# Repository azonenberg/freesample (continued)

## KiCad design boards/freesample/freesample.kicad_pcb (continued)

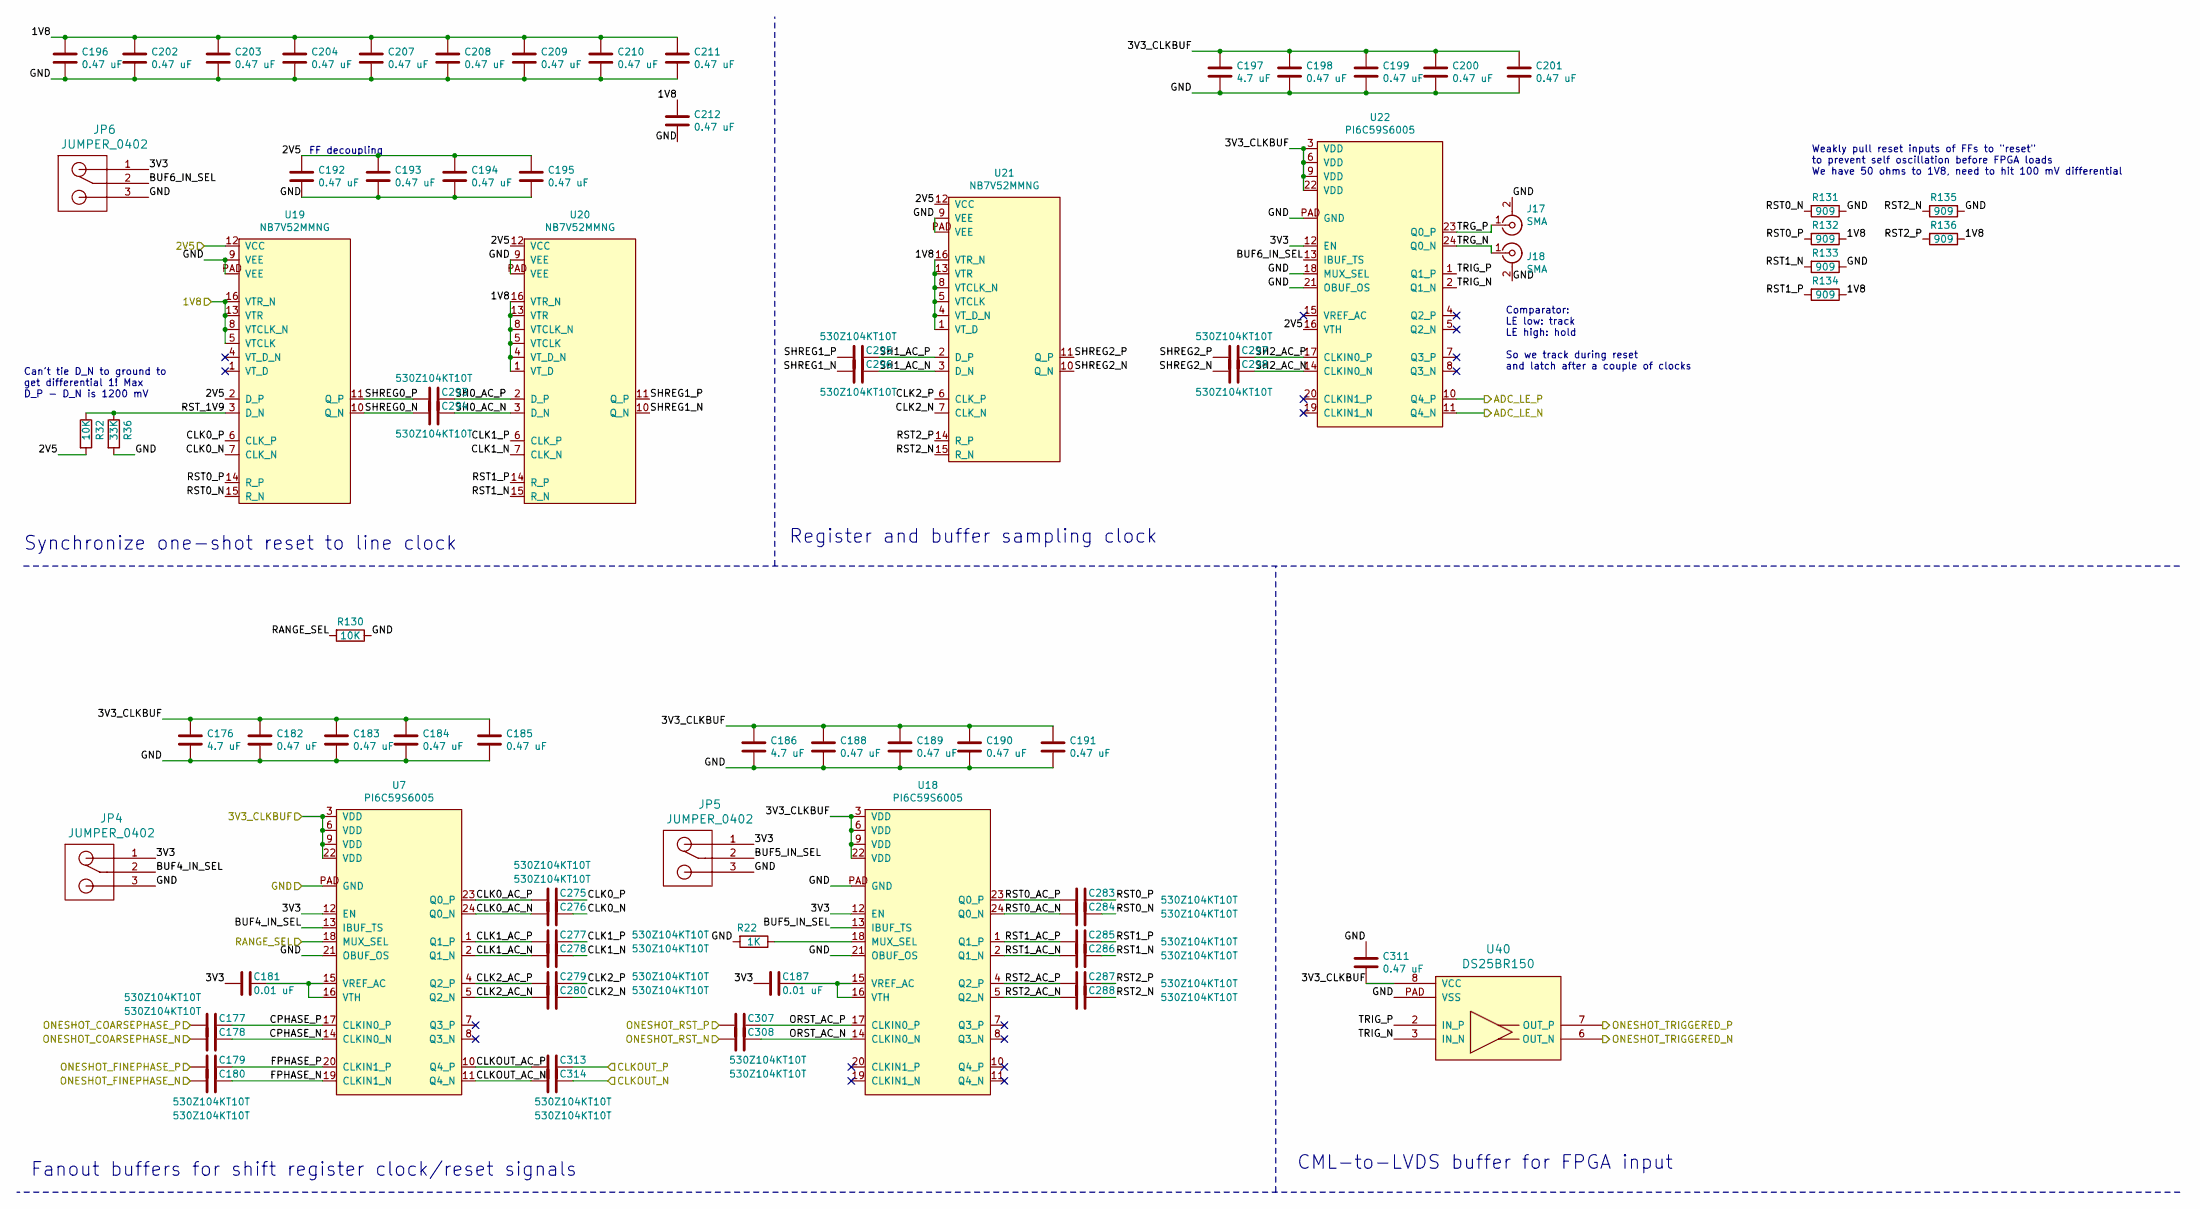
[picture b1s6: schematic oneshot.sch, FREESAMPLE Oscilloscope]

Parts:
C176, C186, C197: 4.7 uF; EIA_0603_CAP_NOSILK
C177, C178, C179, C180, C275, C276, C277, C278, C279, C280, C283, C284, C285, C286, C287, C288, C293, C294, C295, C296, C297, C298, C307, C308, C313, C314: 530Z104KT10T; EIA_0201_CAP_NOSILK
C181, C187: 0.01 uF; EIA_0402_CAP_NOSILK
C182, C183, C184, C185, C188, C189, C190, C191, C192, C193, C194, C195, C196, C198, C199, C200, C201, C202, C203, C204, C207, C208, C209, C210, C211, C212, C311: 0.47 uF; EIA_0402_CAP_NOSILK
J17, J18: SMA; CONN_SMA_EDGE_SAMTEC_SMA_J_P_H_ST_EM1
JP4, JP5, JP6: JUMPER_0402; EIA_0402_JUMPER
R22: 1K; EIA_0402_RES_NOSILK
R32, R130: 10K; EIA_0402_RES_NOSILK
R36: 33K; EIA_0402_RES_NOSILK
R131, R132, R133, R134, R135, R136: 909; EIA_0402_RES_NOSILK
U7, U18, U22: PI6C59S6005; QFN_24_0.5MM_4x4MM
U19, U20, U21: NB7V52MMNG; QFN_16_0.5MM_3x3MM
U40: DS25BR150; DFN_8_0.5MM_3x3MM

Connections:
/1V8: C196.1, C202.1, C203.1, C204.1, C207.1, C208.1, C209.1, C210.1, C211.1, C212.1, R132.1, R134.1, R136.1, U19.5 (VTCLK), U19.8 (VTCLK_N), U19.13 (VTR), U19.16 (VTR_N), U20.1 (VT_D), U20.4 (VT_D_N), U20.5 (VTCLK), U20.8 (VTCLK_N), U20.13 (VTR), U20.16 (VTR_N), U21.1 (VT_D), U21.4 (VT_D_N), U21.5 (VTCLK), U21.8 (VTCLK_N), U21.13 (VTR), U21.16 (VTR_N); also elsewhere on the board
/2V5: C192.1, C193.1, C194.1, C195.1, R32.2, U19.2 (D_P), U19.12 (VCC), U20.12 (VCC), U21.12 (VCC), U22.16 (VTH); also elsewhere on the board
/3V3_CLKBUF: C176.1, C182.1, C183.1, C184.1, C185.1, C186.1, C188.1, C189.1, C190.1, C191.1, C197.1, C198.1, C199.1, C200.1, C201.1, C311.2, U7.3 (VDD), U7.6 (VDD), U7.9 (VDD), U7.22 (VDD), U18.3 (VDD), U18.6 (VDD), U18.9 (VDD), U18.22 (VDD), U22.3 (VDD), U22.6 (VDD), U22.9 (VDD), U22.22 (VDD), U40.8 (VCC); also elsewhere on the board
/ADC/ADC_LE_N: U22.11 (Q4_N); also elsewhere on the board
/ADC/ADC_LE_P: U22.10 (Q4_P); also elsewhere on the board
/GND: C176.2, C182.2, C183.2, C184.2, C185.2, C186.2, C188.2, C189.2, C190.2, C191.2, C192.2, C193.2, C194.2, C195.2, C196.2, C197.2, C198.2, C199.2, C200.2, C201.2, C202.2, C203.2, C204.2, C207.2, C208.2, C209.2, C210.2, C211.2, C212.2, C311.1, J17.2 (Ext), J18.2 (Ext), JP4.3, JP5.3, JP6.3, R22.2, R36.2, R130.1, R131.1, R133.1, R135.1, U7.21 (OBUF_OS), U7.PAD (GND), U18.21 (OBUF_OS), U18.PAD (GND), U19.9 (VEE), U19.PAD (VEE), U20.9 (VEE), U20.PAD (VEE), U21.9 (VEE), U21.PAD (VEE), U22.18 (MUX_SEL), U22.21 (OBUF_OS), U22.PAD (GND), U40.PAD (VSS); also elsewhere on the board
/ONESHOT_RST_N: C308.2; also elsewhere on the board
/ONESHOT_RST_P: C307.2; also elsewhere on the board
/One-Shot/3V3: C181.2, C187.2, JP4.1, JP5.1, JP6.1, U7.12 (EN), U18.12 (EN), U22.12 (EN)
/One-Shot/BUF4_IN_SEL: JP4.2, U7.13 (IBUF_TS)
/One-Shot/BUF5_IN_SEL: JP5.2, U18.13 (IBUF_TS)
/One-Shot/BUF6_IN_SEL: JP6.2, U22.13 (IBUF_TS)
/One-Shot/CLK0_AC_N: C276.2, U7.24 (Q0_N)
/One-Shot/CLK0_AC_P: C275.2, U7.23 (Q0_P)
/One-Shot/CLK0_N: C276.1, U19.7 (CLK_N)
/One-Shot/CLK0_P: C275.1, U19.6 (CLK_P)
/One-Shot/CLK1_AC_N: C278.2, U7.2 (Q1_N)
/One-Shot/CLK1_AC_P: C277.2, U7.1 (Q1_P)
/One-Shot/CLK1_N: C278.1, U20.7 (CLK_N)
/One-Shot/CLK1_P: C277.1, U20.6 (CLK_P)
/One-Shot/CLK2_AC_N: C280.2, U7.5 (Q2_N)
/One-Shot/CLK2_AC_P: C279.2, U7.4 (Q2_P)
/One-Shot/CLK2_N: C280.1, U21.7 (CLK_N)
/One-Shot/CLK2_P: C279.1, U21.6 (CLK_P)
/One-Shot/CLKOUT_AC_N: C314.2, U7.11 (Q4_N)
/One-Shot/CLKOUT_AC_P: C313.2, U7.10 (Q4_P)
/One-Shot/CLKOUT_N: C314.1; also elsewhere on the board
/One-Shot/CLKOUT_P: C313.1; also elsewhere on the board
/One-Shot/CPHASE_N: C178.1, U7.14 (CLKIN0_N)
/One-Shot/CPHASE_P: C177.1, U7.17 (CLKIN0_P)
/One-Shot/FPHASE_N: C180.1, U7.19 (CLKIN1_N)
/One-Shot/FPHASE_P: C179.1, U7.20 (CLKIN1_P)
/One-Shot/ORST_AC_N: C308.1, U18.14 (CLKIN0_N)
/One-Shot/ORST_AC_P: C307.1, U18.17 (CLKIN0_P)
/One-Shot/RST0_AC_N: C284.2, U18.24 (Q0_N)
/One-Shot/RST0_AC_P: C283.2, U18.23 (Q0_P)
/One-Shot/RST0_N: C284.1, R131.2, U19.15 (R_N)
/One-Shot/RST0_P: C283.1, R132.2, U19.14 (R_P)
/One-Shot/RST1_AC_N: C286.2, U18.2 (Q1_N)
/One-Shot/RST1_AC_P: C285.2, U18.1 (Q1_P)
/One-Shot/RST1_N: C286.1, R133.2, U20.15 (R_N)
/One-Shot/RST1_P: C285.1, R134.2, U20.14 (R_P)
/One-Shot/RST2_AC_N: C288.2, U18.5 (Q2_N)
/One-Shot/RST2_AC_P: C287.2, U18.4 (Q2_P)
/One-Shot/RST2_N: C288.1, R135.2, U21.15 (R_N)
/One-Shot/RST2_P: C287.1, R136.2, U21.14 (R_P)
/One-Shot/RST_1V9: R32.1, R36.1, U19.3 (D_N)
/One-Shot/SH0_AC_N: C294.1, U20.3 (D_N)
/One-Shot/SH0_AC_P: C293.1, U20.2 (D_P)
/One-Shot/SH1_AC_N: C296.1, U21.3 (D_N)
/One-Shot/SH1_AC_P: C295.1, U21.2 (D_P)
/One-Shot/SH2_AC_N: C298.1, U22.14 (CLKIN0_N)
/One-Shot/SH2_AC_P: C297.1, U22.17 (CLKIN0_P)
/One-Shot/SHREG0_N: C294.2, U19.10 (Q_N)
/One-Shot/SHREG0_P: C293.2, U19.11 (Q_P)
/One-Shot/SHREG1_N: C296.2, U20.10 (Q_N)
/One-Shot/SHREG1_P: C295.2, U20.11 (Q_P)
/One-Shot/SHREG2_N: C298.2, U21.10 (Q_N)
/One-Shot/SHREG2_P: C297.2, U21.11 (Q_P)
/One-Shot/TRG_N: J18.1 (In), U22.24 (Q0_N)
/One-Shot/TRG_P: J17.1 (In), U22.23 (Q0_P)
/One-Shot/TRIG_N: U22.2 (Q1_N), U40.3 (IN_N)
/One-Shot/TRIG_P: U22.1 (Q1_P), U40.2 (IN_P)
/Phase control/COARSEPHASE_N: C178.2; also elsewhere on the board
/Phase control/COARSEPHASE_P: C177.2; also elsewhere on the board
/Phase control/FINEPHASE_N: C180.2; also elsewhere on the board
/Phase control/FINEPHASE_P: C179.2; also elsewhere on the board
/RANGE_SEL: R130.2, U7.18 (MUX_SEL); also elsewhere on the board
/TRIGGERED_N: U40.6 (OUT_N); also elsewhere on the board
/TRIGGERED_P: U40.7 (OUT_P); also elsewhere on the board
unnamed: C181.1, U7.15 (VREF_AC), U7.16 (VTH)
unnamed: C187.1, U18.15 (VREF_AC), U18.16 (VTH)
unnamed: R22.1, U18.18 (MUX_SEL)

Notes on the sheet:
FF decoupling
Synchronize one-shot reset to line clock
Register and buffer sampling clock
Can't tie D_N to ground to get differential 1! Max D_P - D_N is 1200 mV
CML-to-LVDS buffer for FPGA input
Comparator: LE low: track LE high: hold So we track during reset and latch after a couple of clocks
Fanout buffers for shift register clock/reset signals
Weakly pull reset inputs of FFs to "reset" to prevent self oscillation before FPGA loads We have 50 ohms to 1V8, need to hit 100 mV differential

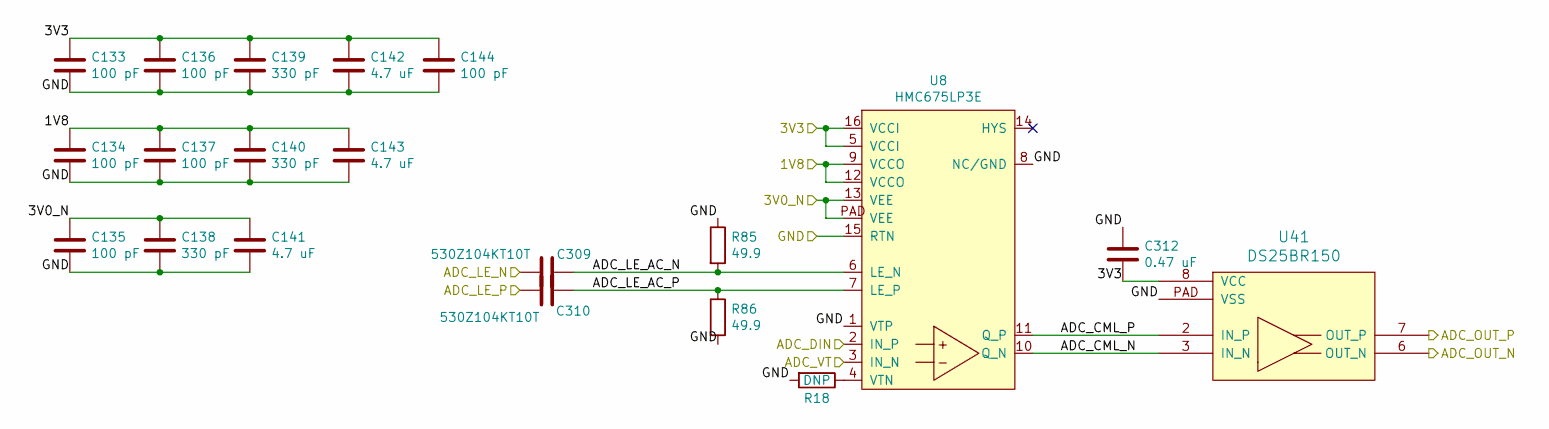
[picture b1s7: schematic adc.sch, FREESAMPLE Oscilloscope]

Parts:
C133, C134, C135, C136, C137, C144: 100 pF; EIA_0201_CAP_NOSILK
C138, C139, C140: 330 pF; EIA_0201_CAP_NOSILK
C141, C142, C143: 4.7 uF; EIA_0603_CAP_NOSILK
C309, C310: 530Z104KT10T; EIA_0201_CAP_NOSILK
C312: 0.47 uF; EIA_0402_CAP_NOSILK
R18: DNP; EIA_0402_RES_NOSILK
R85, R86: 49.9; EIA_0402_RES_NOSILK
U8: HMC675LP3E; QFN_16_0.5MM_3x3MM
U41: DS25BR150; DFN_8_0.5MM_3x3MM

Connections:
/1V8: C134.1, C137.1, C140.1, C143.1, U8.9 (VCCO), U8.12 (VCCO); also elsewhere on the board
/3V0_N: C135.1, C138.1, C141.1, U8.13 (VEE), U8.PAD (VEE); also elsewhere on the board
/3V3: C133.1, C136.1, C139.1, C142.1, C144.1, C312.2, U8.5 (VCCI), U8.16 (VCCI), U41.8 (VCC); also elsewhere on the board
/ADC/ADC_CML_N: U8.10 (Q_N), U41.3 (IN_N)
/ADC/ADC_CML_P: U8.11 (Q_P), U41.2 (IN_P)
/ADC/ADC_LE_AC_N: C309.1, R85.2, U8.6 (LE_N)
/ADC/ADC_LE_AC_P: C310.1, R86.1, U8.7 (LE_P)
/ADC/ADC_LE_N: C309.2; also elsewhere on the board
/ADC/ADC_LE_P: C310.2; also elsewhere on the board
/ADC_DIN: U8.2 (IN_P); also elsewhere on the board
/ADC_OUT_N: U41.6 (OUT_N); also elsewhere on the board
/ADC_OUT_P: U41.7 (OUT_P); also elsewhere on the board
/ADC_VT: U8.3 (IN_N); also elsewhere on the board
/GND: C133.2, C134.2, C135.2, C136.2, C137.2, C138.2, C139.2, C140.2, C141.2, C142.2, C143.2, C144.2, C312.1, R18.2, R85.1, R86.2, U8.1 (VTP), U8.8 (NC/GND), U8.15 (RTN), U41.PAD (VSS); also elsewhere on the board
unnamed: R18.1, U8.4 (VTN)

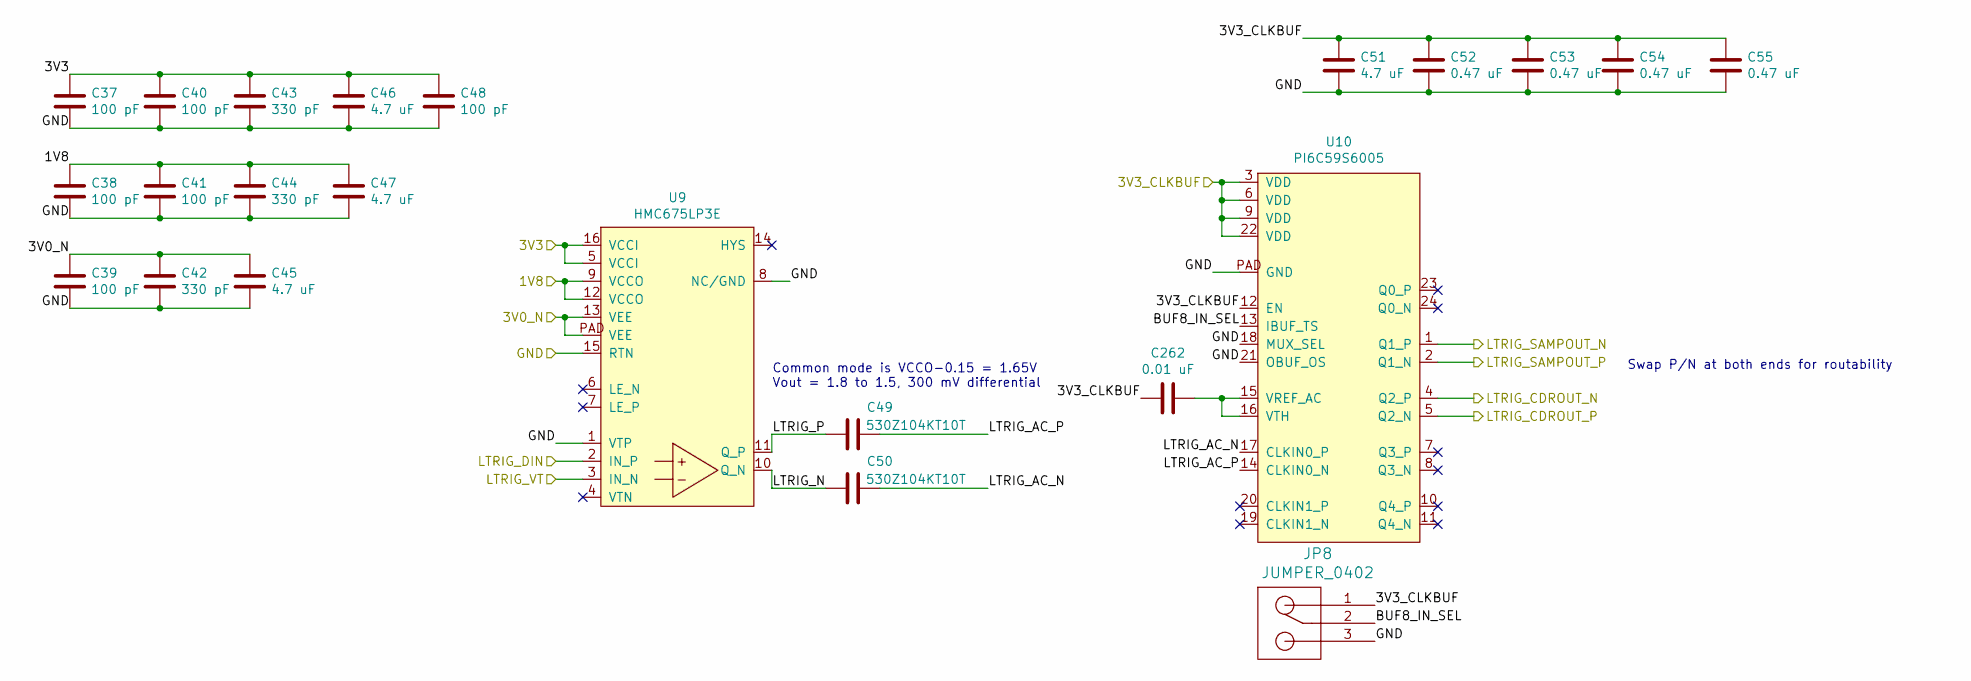
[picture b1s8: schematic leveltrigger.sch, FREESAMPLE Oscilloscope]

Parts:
C37, C38, C39, C40, C41, C48: 100 pF; EIA_0201_CAP_NOSILK
C42, C43, C44: 330 pF; EIA_0201_CAP_NOSILK
C45, C46, C47, C51: 4.7 uF; EIA_0603_CAP_NOSILK
C49, C50: 530Z104KT10T; EIA_0201_CAP_NOSILK
C52, C53, C54, C55: 0.47 uF; EIA_0402_CAP_NOSILK
C262: 0.01 uF; EIA_0402_CAP_NOSILK
JP8: JUMPER_0402; EIA_0402_JUMPER
U9: HMC675LP3E; QFN_16_0.5MM_3x3MM
U10: PI6C59S6005; QFN_24_0.5MM_4x4MM

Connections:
/1V8: C38.1, C41.1, C44.1, C47.1, U9.9 (VCCO), U9.12 (VCCO); also elsewhere on the board
/3V0_N: C39.1, C42.1, C45.1, U9.13 (VEE), U9.PAD (VEE); also elsewhere on the board
/3V3: C37.1, C40.1, C43.1, C46.1, C48.1, U9.5 (VCCI), U9.16 (VCCI); also elsewhere on the board
/3V3_CLKBUF: C51.1, C52.1, C53.1, C54.1, C55.1, C262.2, JP8.1, U10.3 (VDD), U10.6 (VDD), U10.9 (VDD), U10.12 (EN), U10.22 (VDD); also elsewhere on the board
/CDR/CDR_DIN_N: U10.4 (Q2_P); also elsewhere on the board
/CDR/CDR_DIN_P: U10.5 (Q2_N); also elsewhere on the board
/GND: C37.2, C38.2, C39.2, C40.2, C41.2, C42.2, C43.2, C44.2, C45.2, C46.2, C47.2, C48.2, C51.2, C52.2, C53.2, C54.2, C55.2, JP8.3, U9.1 (VTP), U9.8 (NC/GND), U9.15 (RTN), U10.18 (MUX_SEL), U10.21 (OBUF_OS), U10.PAD (GND); also elsewhere on the board
/LTRIG_DIN: U9.2 (IN_P); also elsewhere on the board
/LTRIG_VT: U9.3 (IN_N); also elsewhere on the board
/Level triggering/BUF8_IN_SEL: JP8.2, U10.13 (IBUF_TS)
/Level triggering/LTRIG_AC_N: C50.1, U10.17 (CLKIN0_P)
/Level triggering/LTRIG_AC_P: C49.1, U10.14 (CLKIN0_N)
/Level triggering/LTRIG_N: C50.2, U9.10 (Q_N)
/Level triggering/LTRIG_P: C49.2, U9.11 (Q_P)
/Level triggering/LTRIG_SAMPOUT_N: U10.1 (Q1_P); also elsewhere on the board
/Level triggering/LTRIG_SAMPOUT_P: U10.2 (Q1_N); also elsewhere on the board
unnamed: C262.1, U10.15 (VREF_AC), U10.16 (VTH)

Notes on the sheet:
Common mode is VCCO-0.15 = 1.65V Vout = 1.8 to 1.5, 300 mV differential
Swap P/N at both ends for routability

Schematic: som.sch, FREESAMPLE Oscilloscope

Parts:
C129, C130, C131, C132, C321: 0.1 uF; EIA_0402_CAP_NOSILK
J7: CONN_INTEGRALSTICK_FPGA_HOST; CONN_SAMTEC_QSH-060-01-L-D-A
J8: CONN_INTEGRALSTICK_MCU_HOST; CONN_SAMTEC_QSH-060-01-L-D-A
J9: 0826-1G1T-23-F; CONN_BELFUSE_0826_1G1T_23_F
J10: XILINX_JTAG; XILINX_JTAG_PTH_MOLEX_0878311420
J19, J20, J21: JUMPER; CONN_HEADER_2.54MM_1x2
J24, J25: SMA; CONN_SMA_EDGE_SAMTEC_SMA_J_P_H_ST_EM1
J26: PMOD_HOST; CONN_HEADER_2.54MM_2x6_RA_PMOD_HOST
Q1: SSM6N58NU; DFN_6_0.65MM_2x2MM_GDS
R16, R17: 470; EIA_0402_RES_NOSILK
TP32, TP33, TP34, TP35: GROUNDCLIP; TESTPOINT_SMT_KEYSTONE_5016

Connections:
/5V25: J7.1 (5V0), J7.2 (5V0), J7.3 (5V0), J7.4 (5V0), J7.5 (5V0), J7.6 (5V0); also elsewhere on the board
/ADC_OUT_N: J7.16 (LVDS_DQ6_N); also elsewhere on the board
/ADC_OUT_P: J7.18 (LVDS_DQ6_P); also elsewhere on the board
/COARSE_EN: J7.97 (IO_3V3); also elsewhere on the board
/COARSE_SCLK: J7.102 (IO_3V3); also elsewhere on the board
/COARSE_SDIN: J7.101 (IO_3V3); also elsewhere on the board
/COARSE_SLOAD: J7.98 (IO_3V3); also elsewhere on the board
/D3V3: J7.69 (3V3), J7.70 (3V3), J7.75 (3V3), J7.76 (3V3), J7.81 (3V3), J7.82 (3V3), J7.87 (3V3), J7.88 (3V3), J7.93 (3V3), J7.94 (3V3), J7.99 (3V3), J7.100 (3V3), J7.105 (3V3), J7.106 (3V3), J7.111 (3V3), J7.112 (3V3), J7.117 (3V3), J7.118 (3V3), J8.1 (3V3), J8.7 (3V3), J8.13 (3V3), J8.19 (3V3), J8.25 (3V3), J8.31 (3V3), J8.32 (3V3), J8.37 (3V3), J8.38 (3V3), J8.43 (3V3), J8.44 (3V3), J8.49 (3V3), J8.50 (3V3), J8.55 (3V3), J8.56 (3V3), J8.61 (3V3), J8.62 (3V3), J8.67 (3V3), J8.68 (3V3), J8.73 (3V3), J8.74 (3V3), J8.79 (3V3), J8.80 (3V3), J8.85 (3V3), J8.86 (3V3), J8.91 (3V3), J8.92 (3V3), J8.97 (3V3), J8.98 (3V3), J8.103 (3V3), J8.104 (3V3), J8.109 (3V3), J8.110 (3V3), J8.115 (3V3), J8.116 (3V3), J10.2 (Vccaux), J21.2, J26.6 (3V3), J26.12 (3V3), R16.2, R17.2; also elsewhere on the board
/DAC_CS_N: J7.67 (IO_1V8); also elsewhere on the board
/DAC_MISO: J7.62 (IO_1V8); also elsewhere on the board
/DAC_MOSI: J7.65 (IO_1V8); also elsewhere on the board
/DAC_MUXOUT: J8.111 (PF3); also elsewhere on the board
/DAC_RST_N: J7.61 (IO_1V8); also elsewhere on the board
/DAC_SCK: J7.66 (IO_1V8); also elsewhere on the board
/EXT_CLK_SEL: J7.73 (IO_3V3); also elsewhere on the board
/FINE_SEL0_N: J7.34 (LVDS_DQ0_N); also elsewhere on the board
/FINE_SEL0_P: J7.36 (LVDS_DQ0_P); also elsewhere on the board
/FINE_SEL1_N: J7.33 (LVDS_DQ1_N); also elsewhere on the board
/FINE_SEL1_P: J7.35 (LVDS_DQ1_P); also elsewhere on the board
/FINE_SEL2_N: J7.28 (LVDS_DQ2_N); also elsewhere on the board
/FINE_SEL2_P: J7.30 (LVDS_DQ2_P); also elsewhere on the board
/FINE_SEL3_N: J7.27 (LVDS_DQ3_N); also elsewhere on the board
/FINE_SEL3_P: J7.29 (LVDS_DQ3_P); also elsewhere on the board
/FINE_SEL4_N: J7.22 (LVDS_DQ4_N); also elsewhere on the board
/FINE_SEL4_P: J7.24 (LVDS_DQ4_P); also elsewhere on the board
/FPGACLK_N: J7.107 (IO_3V3_CKN); also elsewhere on the board
/FPGACLK_P: J7.109 (IO_3V3_CKP); also elsewhere on the board
/GND: C129.1, C130.1, C131.1, C132.1, C321.2, J7.121 (GND), J7.122 (GND), J7.123 (GND), J7.124 (GND), J7.125 (GND), J7.126 (GND), J7.127 (GND), J7.128 (GND), J8.2 (GND), J8.8 (GND), J8.14 (GND), J8.20 (GND), J8.26 (GND), J8.121 (GND), J8.122 (GND), J8.123 (GND), J8.124 (GND), J8.125 (GND), J8.126 (GND), J8.127 (GND), J8.128 (GND), J10.3 (Vss), J10.5 (Vss), J10.7 (Vss), J10.9 (Vss), J10.11 (Vss), J19.2, J20.2, J24.2 (Ext), J25.2 (Ext), J26.5 (GND), J26.11 (GND), Q1.S1 (S), Q1.S2 (S), TP32.1, TP33.1, TP34.1, TP35.1; also elsewhere on the board
/LDAC_N: J7.68 (IO_1V8); also elsewhere on the board
/ONESHOT_RST_N: J7.21 (LVDS_DQ5_N); also elsewhere on the board
/ONESHOT_RST_P: J7.23 (LVDS_DQ5_P); also elsewhere on the board
/OSC_FS0: J7.79 (IO_3V3); also elsewhere on the board
/OSC_FS1: J7.78 (IO_3V3); also elsewhere on the board
/OSC_OE: J7.74 (IO_3V3); also elsewhere on the board
/OSC_OS: J7.77 (IO_3V3); also elsewhere on the board
/OSC_PWR_EN: J7.103 (IO_3V3); also elsewhere on the board
/PLL_CLK: J7.86 (IO_3V3); also elsewhere on the board
/PLL_CLKIN0: J7.90 (IO_3V3); also elsewhere on the board
/PLL_CLKIN1: J7.91 (IO_3V3); also elsewhere on the board
/PLL_DATA: J7.89 (IO_3V3); also elsewhere on the board
/PLL_HOLDOVER: J7.83 (IO_3V3); also elsewhere on the board
/PLL_LD: J7.84 (IO_3V3); also elsewhere on the board
/PLL_LE: J7.85 (IO_3V3); also elsewhere on the board
/PLL_SYNC: J7.80 (IO_3V3); also elsewhere on the board
/RANGE_SEL: J7.96 (IO_3V3); also elsewhere on the board
/SAMP_MUXSEL0: J7.92 (IO_3V3); also elsewhere on the board
/SAMP_MUXSEL1: J7.95 (IO_3V3); also elsewhere on the board
/SERDES_MDC: J7.56 (IO_1V8); also elsewhere on the board
/SERDES_MDIO: J7.55 (IO_1V8); also elsewhere on the board
/SERDES_MODE_SEL: J7.60 (IO_1V8); also elsewhere on the board
/SERDES_POWER_EN: J7.54 (IO_1V8); also elsewhere on the board
/SERDES_RST_N: J7.59 (IO_1V8); also elsewhere on the board
/SoM connectors/D1V8: J7.39 (1V8), J7.40 (1V8), J7.45 (1V8), J7.46 (1V8), J7.51 (1V8), J7.52 (1V8), J7.57 (1V8), J7.58 (1V8), J7.63 (1V8), J7.64 (1V8)
/SoM connectors/D2V5: J7.7 (2V5), J7.8 (2V5), J7.13 (2V5), J7.14 (2V5), J7.19 (2V5), J7.20 (2V5), J7.25 (2V5), J7.26 (2V5), J7.31 (2V5), J7.32 (2V5), J7.37 (2V5), J7.38 (2V5)
/SoM connectors/ETH_A_N: J8.6 (ETH_A_N), J9.10 (CH1_N)
/SoM connectors/ETH_A_P: J8.4 (ETH_A_P), J9.11 (CH1_P)
/SoM connectors/ETH_A_TAP: C129.2, J9.12 (CH1_TAP)
/SoM connectors/ETH_B_N: J8.12 (ETH_B_N), J9.5 (CH2_N)
/SoM connectors/ETH_B_P: J8.10 (ETH_B_P), J9.4 (CH2_P)
/SoM connectors/ETH_B_TAP: C130.2, J9.6 (CH2_TAP)
/SoM connectors/ETH_C_N: J8.18 (ETH_C_N), J9.2 (CH3_N)
/SoM connectors/ETH_C_P: J8.16 (ETH_C_P), J9.3 (CH3_P)
/SoM connectors/ETH_C_TAP: C131.2, J9.1 (CH3_TAP)
/SoM connectors/ETH_D_N: J8.24 (ETH_D_N), J9.9 (CH4_N)
/SoM connectors/ETH_D_P: J8.22 (ETH_D_P), J9.8 (CH4_P)
/SoM connectors/ETH_D_TAP: C132.2, J9.7 (CH4_TAP)
/SoM connectors/ETH_GND: C321.1, J9.17 (SHLD)
/SoM connectors/ETH_LED1_EN: J7.50 (IO_1V8), Q1.G2 (G)
/SoM connectors/ETH_LED1_N: J9.13 (LED1_N), Q1.D2 (D)
/SoM connectors/ETH_LED2_EN: J7.53 (IO_1V8), Q1.G1 (G)
/SoM connectors/ETH_LED2_N: J9.15 (LED2_N), Q1.D1 (D)
/SoM connectors/FPGA_RST_N: J8.76 (FPGA_RST_N), J19.1
/SoM connectors/GPIO0: J7.110 (IO_3V3), J26.1 (D0)
/SoM connectors/GPIO1: J7.113 (IO_3V3), J26.2 (D1)
/SoM connectors/GPIO2: J7.114 (IO_3V3), J26.3 (D2)
/SoM connectors/GPIO3: J7.115 (IO_3V3), J26.4 (D3)
/SoM connectors/GPIO4: J7.116 (IO_3V3), J26.7 (D4)
/SoM connectors/GPIO5: J7.119 (IO_3V3), J26.8 (D5)
/SoM connectors/GPIO6: J7.120 (IO_3V3), J26.9 (D6)
/SoM connectors/GPIO7: J7.104 (IO_3V3), J26.10 (D7)
/SoM connectors/JTAG_TCK: J8.64 (TCK), J10.6 (TCK)
/SoM connectors/JTAG_TDI: J8.66 (TDI), J10.10 (TDI_OUT)
/SoM connectors/JTAG_TDO: J8.72 (TDO), J10.8 (TDO_IN)
/SoM connectors/JTAG_TMS: J8.70 (TMS), J10.4 (TMS)
/SoM connectors/MCU_BOOT0: J8.78 (MCU_BOOT0), J21.1
/SoM connectors/MCU_RST_N: J8.113 (MCU_RST_N), J20.1
/SoM connectors/SMA_GPIO_N: J7.10 (LVDS_DQ8_N), J25.1 (In)
/SoM connectors/SMA_GPIO_P: J7.12 (LVDS_DQ8_P), J24.1 (In)
/TRIGGERED_N: J7.15 (LVDS_DQ7_N); also elsewhere on the board
/TRIGGERED_P: J7.17 (LVDS_DQ7_P); also elsewhere on the board
unnamed: J9.14 (LED1_P), R16.1
unnamed: J9.16 (LED2_P), R17.1

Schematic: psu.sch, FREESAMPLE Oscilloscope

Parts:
C219: 4.7 uF 12V; EIA_1206_CAP_NOSILK
C220, C221, C222, C253, C254, C258, C259: 4.7 uF 5V; EIA_1206_CAP_NOSILK
C223, C256, C260: 2.2 uF 5V; EIA_0603_CAP_NOSILK
C224, C257, C261: 1 uF 5V; EIA_0603_CAP_NOSILK
C225, C230, C241, C242, C246, C247, C248, C249, C317, C318, C319, C320: 4.7 uF; EIA_0603_CAP_NOSILK
C226, C229: 1 uF; EIA_0603_CAP_NOSILK
C227: 22 nF; EIA_0402_CAP_NOSILK
C228, C232, C233, C234: 22 uF; EIA_0805_CAP_NOSILK
C231: 1 uF; EIA_0402_CAP_NOSILK
C235, C237, C240, C243, C250, C252: 22 uF 16V; EIA_1812_CAP_NOSILK
C236, C238, C251, C255: 22 uF 10V; EIA_1210_CAP_NOSILK
C239, C244, C245, C315, C316: 10 nF; EIA_0402_CAP_NOSILK
R28: 309K 1%; EIA_0402_RES_NOSILK
R29, R67, R73: 100K 1%; EIA_0402_RES_NOSILK
R30: 1K; EIA_0402_RES_NOSILK
R31, R35, R43, R47, R49, R50, R57, R61, R65, R71, R87, R88: 0; EIA_0402_RES_NOSILK
R33, R34: 5 mR; EIA_0603_RES_NOSILK
R37: 10.5K; EIA_0402_RES_NOSILK
R38, R42, R59, R63, R69: 20K; EIA_0402_RES_NOSILK
R39, R46, R60, R64, R70: 10K; EIA_0402_RES_NOSILK
R40: DNP; EIA_0402_RES_NOSILK
R41: 1.27K; EIA_0402_RES_NOSILK
R44, R51, R52: 113K; EIA_0402_RES_NOSILK
R45, R53, R54, R91, R92: 100K; EIA_0402_RES_NOSILK
R48: 20K 0.1%; EIA_0402_RES_NOSILK
R55, R56, R93, R94: 20K 1%; EIA_0402_RES_NOSILK
R58, R62: 2.05K; EIA_0402_RES_NOSILK
R66: 147K 1%; EIA_0402_RES_NOSILK
R68: 2.8K; EIA_0402_RES_NOSILK
R72: 174k 1%; EIA_0402_RES_NOSILK
R89: 80.6K; EIA_0402_RES_NOSILK
R90: 52.3K; EIA_0402_RES_NOSILK
R112, R113: 953; EIA_0402_RES_NOSILK
R114, R115, R116, R117, R118, R119, R120, R121, R122, R123, R124, R125, R126, R127: 453; EIA_0402_RES_NOSILK
TP3, TP4, TP5, TP6, TP7, TP8, TP9, TP10, TP11, TP12, TP13, TP14, TP15, TP16, TP17, TP18: HEADER; CONN_HEADER_2.54MM_1x2
TP19, TP20: TESTCLIP; TESTPOINT_SMT_KEYSTONE_5016
TP21, TP22, TP23, TP24, TP25, TP26, TP27, TP28, TP29, TP30, TP31: PROBEPAD; TESTPOINT_SMT_0.5MM
U26: MCP1755ST-5002E/MC; DFN_8_0.5MM_3x3MM
U27, U37, U39: LM27761; DFN_8_0.5MM_2x2MM
U28, U29: ADP1763Z-1.0; QFN_16_0.5MM_3x3MM
U30, U32, U35, U36, U38: OKL-T/3-W12P-C; MODULE_MURATA_OKL-T3-W12
U31, U33, U34, U42, U43: ADP1741; QFN_16_0.65MM_4x4MM

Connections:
/1V0: C233.1, C234.1, R31.1, R33.1, R34.1, R35.1, R115.2; also elsewhere on the board
/1V8: C320.2, R88.2, R125.2, U43.10 (VOUT), U43.11 (VOUT), U43.12 (VOUT), U43.13 (VOUT), U43.14 (VOUT); also elsewhere on the board
/2V5: C319.2, R87.2, R124.2, U42.10 (VOUT), U42.11 (VOUT), U42.12 (VOUT), U42.13 (VOUT), U42.14 (VOUT); also elsewhere on the board
/3V0_N: C256.2, R122.2, U37.4 (VOUT); also elsewhere on the board
/3V3: C249.2, R50.2, R119.2, U34.10 (VOUT), U34.11 (VOUT), U34.12 (VOUT), U34.13 (VOUT), U34.14 (VOUT); also elsewhere on the board
/3V3_CLKBUF: C242.2, R43.2, R117.2, U31.10 (VOUT), U31.11 (VOUT), U31.12 (VOUT), U31.13 (VOUT), U31.14 (VOUT); also elsewhere on the board
/3V3_N: C260.2, R123.2, U39.4 (VOUT); also elsewhere on the board
/3V3_PLL: C248.2, R49.2, R118.2, U33.10 (VOUT), U33.11 (VOUT), U33.12 (VOUT), U33.13 (VOUT), U33.14 (VOUT); also elsewhere on the board
/5V0_N: C223.2, R28.1, R66.1, R72.1, R113.2, U27.4 (VOUT); also elsewhere on the board
/5V25: C221.1, C243.1, R47.1, R116.2, U27.1 (VIN), U27.6 (EN), U32.4 (VOUT); also elsewhere on the board
/12V0: C219.1, C235.1, C237.1, C240.1, C250.1, C252.1, R38.2, R42.2, R59.2, R63.2, R69.2, R127.2, U26.8 (VIN), U30.2 (VIN), U32.2 (VIN), U35.2 (VIN), U36.2 (VIN), U38.2 (VIN); also elsewhere on the board
/A5V0: C220.1, R112.2, U26.1 (VOUT); also elsewhere on the board
/D3V3: R30.2, R39.1, R45.1, R46.1, R53.1, R54.1, R60.1, R64.1, R70.1, R91.1, R92.1; also elsewhere on the board
/GND: C219.2, C220.2, C221.2, C222.1, C223.1, C225.2, C226.2, C227.1, C228.2, C229.2, C230.2, C231.1, C232.2, C233.2, C234.2, C235.2, C236.2, C237.2, C238.2, C239.2, C240.2, C241.2, C242.1, C243.2, C244.2, C245.2, C246.2, C247.2, C248.1, C249.1, C250.2, C251.2, C252.2, C253.2, C254.1, C255.2, C256.1, C258.2, C259.1, C260.1, C315.2, C316.2, C317.2, C318.2, C319.1, C320.1, R29.1, R37.1, R40.2, R41.1, R48.1, R55.1, R56.1, R58.1, R62.1, R67.1, R68.1, R73.1, R93.1, R94.1, TP3.2, TP4.2, TP5.2, TP6.2, TP7.2, TP8.2, TP9.2, TP10.2, TP11.2, TP12.2, TP13.2, TP14.2, TP15.2, TP16.2, TP17.2, TP18.2, TP19.1, TP20.1, U26.4 (GND), U26.PAD (GND), U27.2 (GND), U27.PAD (GND), U28.7 (GND), U28.PAD (GND), U29.7 (GND), U29.PAD (GND), U30.3 (GND), U30.7 (GND), U31.6 (GND), U31.PAD (GND), U32.3 (GND), U32.7 (GND), U33.6 (GND), U33.PAD (GND), U34.6 (GND), U34.PAD (GND), U35.3 (GND), U35.7 (GND), U36.3 (GND), U36.7 (GND), U37.2 (GND), U37.PAD (GND), U38.3 (GND), U38.7 (GND), U39.2 (GND), U39.PAD (GND), U42.6 (GND), U42.PAD (GND), U43.6 (GND), U43.PAD (GND); also elsewhere on the board
/Power supply/1V0_PGOOD: R30.1, TP22.1, U28.15 (PG), U29.15 (PG)
/Power supply/1V0_REF: C229.1, U28.5 (REFCAP), U29.5 (REFCAP)
/Power supply/1V0_SENSE: R31.2, R35.2, U28.13 (SENSE), U29.13 (SENSE)
/Power supply/1V0_SS: C227.2, U28.14 (SS), U29.14 (SS)
/Power supply/1V0_VADJ: R40.1, U28.8 (VADJ), U29.8 (VADJ)
/Power supply/1V1_PGOOD: R39.2, TP21.1, U30.10 (PGOOD)
/Power supply/1V1_SENSE: R57.2, U30.5 (SENSE)
/Power supply/1V8_PGOOD: R92.2, TP24.1, U43.5 (PG)
/Power supply/1V8_SENSE: R88.1, R90.1
/Power supply/1V15_INT: C225.1, C228.1, C230.1, C232.1, C236.1, R57.1, R114.2, U28.1 (VIN), U28.2 (VIN), U28.3 (VIN), U28.4 (VIN), U28.16 (EN), U29.1 (VIN), U29.2 (VIN), U29.3 (VIN), U29.4 (VIN), U29.16 (EN), U30.4 (VOUT)
/Power supply/2V5_PGOOD: R91.2, TP25.1, U42.5 (PG)
/Power supply/2V5_SENSE: R87.1, R89.1
/Power supply/2V7_INT: C255.1, C317.1, C318.1, R71.1, R126.2, U38.4 (VOUT), U42.1 (VIN), U42.2 (VIN), U42.3 (VIN), U42.4 (EN), U42.15 (VIN), U42.16 (VIN), U43.1 (VIN), U43.2 (VIN), U43.3 (VIN), U43.4 (EN), U43.15 (VIN), U43.16 (VIN)
/Power supply/2V7_PGOOD: R70.2, TP31.1, U38.10 (PGOOD)
/Power supply/2V7_SENSE: R71.2, U38.5 (SENSE)
/Power supply/3V0_N_FB: R66.2, R67.2, U37.5 (VFB)
/Power supply/3V3_CLKBUF_PGOOD: R45.2, TP27.1, U31.5 (PG)
/Power supply/3V3_CLKBUF_SENSE: R43.1, R44.1
/Power supply/3V3_N_FB: R72.2, R73.2, U39.5 (VFB)
/Power supply/3V3_PGOOD: R54.2, TP29.1, U34.5 (PG)
/Power supply/3V3_PLL_PGOOD: R53.2, TP28.1, U33.5 (PG)
/Power supply/3V3_PLL_SENSE: R49.1, R51.1
/Power supply/3V3_SENSE: R50.1, R52.1
/Power supply/3V5_INT1: C238.1, C246.1, C247.1, C253.1, C258.1, R61.1, R120.2, U31.4 (EN), U33.1 (VIN), U33.2 (VIN), U33.3 (VIN), U33.4 (EN), U33.15 (VIN), U33.16 (VIN), U34.1 (VIN), U34.2 (VIN), U34.3 (VIN), U34.4 (EN), U34.15 (VIN), U34.16 (VIN), U35.4 (VOUT), U37.1 (VIN), U37.6 (EN), U39.1 (VIN), U39.6 (EN)
/Power supply/3V5_INT2: C241.1, C251.1, R65.1, R121.2, U31.1 (VIN), U31.2 (VIN), U31.3 (VIN), U31.15 (VIN), U31.16 (VIN), U36.4 (VOUT)
/Power supply/3V5_PGOOD: R60.2, TP23.1, U35.10 (PGOOD)
/Power supply/3V5_PGOOD2: R64.2, TP30.1, U36.10 (PGOOD)
/Power supply/3V5_SENSE: R61.2, U35.5 (SENSE)
/Power supply/3V5_SENSE2: R65.2, U36.5 (SENSE)
/Power supply/5V0_N_FB: R28.2, R29.2, U27.5 (VFB)
/Power supply/5V0_PGOOD: R46.2, TP26.1, U32.10 (PGOOD)
/Power supply/5V0_SENSE: R47.2, U32.5 (SENSE)
unnamed: C222.2, U27.3 (CPOUT)
unnamed: C224.1, U27.7 (C1-)
unnamed: C224.2, U27.8 (C1+)
unnamed: C226.1, U28.6 (VREG)
unnamed: C231.2, U29.6 (VREG)
unnamed: C239.1, U31.7 (SS)
unnamed: C244.1, U33.7 (SS)
unnamed: C245.1, U34.7 (SS)
unnamed: C254.2, U37.3 (CPOUT)
unnamed: C257.1, U37.7 (C1-)
unnamed: C257.2, U37.8 (C1+)
unnamed: C259.2, U39.3 (CPOUT)
unnamed: C261.1, U39.7 (C1-)
unnamed: C261.2, U39.8 (C1+)
unnamed: C315.1, U42.7 (SS)
unnamed: C316.1, U43.7 (SS)
unnamed: R33.2, U28.9 (VOUT), U28.10 (VOUT), U28.11 (VOUT), U28.12 (VOUT)
unnamed: R34.2, U29.9 (VOUT), U29.10 (VOUT), U29.11 (VOUT), U29.12 (VOUT)
unnamed: R37.2, U30.6 (TRIM)
unnamed: R38.1, U30.1 (EN)
unnamed: R41.2, U32.6 (TRIM)
unnamed: R42.1, U32.1 (EN)
unnamed: R44.2, R48.2, U31.9 (ADJ)
unnamed: R51.2, R55.2, U33.9 (ADJ)
unnamed: R52.2, R56.2, U34.9 (ADJ)
unnamed: R58.2, U35.6 (TRIM)
unnamed: R59.1, U35.1 (EN)
unnamed: R62.2, U36.6 (TRIM)
unnamed: R63.1, U36.1 (EN)
unnamed: R68.2, U38.6 (TRIM)
unnamed: R69.1, U38.1 (EN)
unnamed: R89.2, R93.2, U42.9 (ADJ)
unnamed: R90.2, R94.2, U43.9 (ADJ)
unnamed: R112.1, TP3.1
unnamed: R113.1, TP4.1
unnamed: R114.1, TP5.1
unnamed: R115.1, TP6.1
unnamed: R116.1, TP7.1
unnamed: R117.1, TP8.1
unnamed: R118.1, TP9.1
unnamed: R119.1, TP10.1
unnamed: R120.1, TP11.1
unnamed: R121.1, TP12.1
unnamed: R122.1, TP13.1
unnamed: R123.1, TP14.1
unnamed: R124.1, TP15.1
unnamed: R125.1, TP16.1
unnamed: R126.1, TP17.1
unnamed: R127.1, TP18.1

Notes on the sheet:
A5V0: estimated 3 mA from 12V in Conservatively: 4.9C rise (70 mW) at 10 mA
5V0_N: estimated 3 mA from 5.25V in Vout = -1.22 * (R28+R29)/R29 R29 > 50 kR (use 100K) Use 309K (ideal 309.836K) for -4.99V SMPS w/ 3 mA load, no thermal analysis necessary
Vout = 3.0 * (Radj * 50 uA) Radj = 1V/(150 uA) = 6.667 kR Use 6.65K for 0.9975V Connect two in parallel to spread out heat generation 0.15V * 3A = 0.45W total, estimate 0.3W worst case per chip Assuming 1cm^2 plane for heatsinking, 30.8C rise. Bigger planes will improve this Typical SERDES power is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
-5V analog supply (3 mA)
+5V analog supply (<10 mA)
1.15V intermediate rail (2.6A)
1.0V CDR SERDES supply (2.6A)
+5.25V supply for INTEGRALSTICK (<1A typ)
+3.3V supply for clock buffers (1.4A)
+3.3V supply for PLL and VCO (0.85A)
+3.3V supply for other loads (0.25A)
+3.5V intermediate rail 1 (1.4A)
0.2V drop * 0.85A = 0.17W 7.14C rise
0.2V drop * 2A = 0.4W 16.8C rise Vout = 0.5*(1 + R44/R48), R48 < 60 kR R44=113K gives 3.325V
0.2V drop * 0.25A = 0.05W 2.1C rise
Rtrim(k) = 5.91 / (5.25 - 0.591) = 1.27K
Rtrim(k) = 5.91 / (3.5 - 0.591) = 2.03K nominal
Rtrim(k) = 5.91 / (1.15 - 0.591) = 10.57K nominal
+2.7V intermediate rail (0.7A)
Rtrim(k) = 5.91 / (2.7 - 0.591) = 2.80K nominal
+2.5V supply for flipflops (0.5A)
+1.8V supply for SERDES/comparators (0.2A)
-3.0V supply for comparators (0.1A)
-3.3V supply for delay line (0.2A)
+3.5V intermediate rail 2 (1.4A)
3V0_N: estimated 100 mA from 3.5V in Vout = -1.22 * (R66+R67)/R67 R67 > 50 kR (use 100K) Use 147k (ideal 145.9k) for -3.0V Thermal analysis TODO
3V3_N: estimated 100 mA from 3.5V in Vout = -1.22 * (R66+R67)/R67 R67 > 50 kR (use 100K) Use 174k (ideal 170.5k) for -3.3V Thermal analysis TODO
0.2V drop * 0.5A = 0.1W 4.2C rise
0.9V drop * 0.2A = 0.18W 7.6C rise
Test points for power rails Integrated 10x low-Z probes
Test points for low current power rails Integrated 20x low-Z probes
Test points for power-good signals

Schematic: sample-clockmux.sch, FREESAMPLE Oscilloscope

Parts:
C145, C158: 4.7 uF; EIA_0603_CAP_NOSILK
C146, C147, C148, C149, C155, C156, C205, C206: 530Z104KT10T; EIA_0201_CAP_NOSILK
C150, C151, C152, C153, C159, C160, C161, C162: 0.47 uF; EIA_0402_CAP_NOSILK
C154, C157: 0.01 uF; EIA_0402_CAP_NOSILK
J15, J16: SMA; CONN_SMA_EDGE_SAMTEC_SMA_J_P_H_ST_EM1
JP2, JP3: JUMPER_0402; EIA_0402_JUMPER
R128, R129: 10K; EIA_0402_RES_NOSILK
U11, U12: PI6C59S6005; QFN_24_0.5MM_4x4MM

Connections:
/3V3_CLKBUF: C145.1, C150.1, C151.1, C152.1, C153.1, C154.2, C157.2, C158.1, C159.1, C160.1, C161.1, C162.1, JP2.1, JP3.1, U11.3 (VDD), U11.6 (VDD), U11.9 (VDD), U11.12 (EN), U11.22 (VDD), U12.3 (VDD), U12.6 (VDD), U12.9 (VDD), U12.12 (EN), U12.22 (VDD); also elsewhere on the board
/GND: C145.2, C150.2, C151.2, C152.2, C153.2, C158.2, C159.2, C160.2, C161.2, C162.2, J15.2 (Ext), J16.2 (Ext), JP2.3, JP3.3, R128.2, R129.2, U11.21 (OBUF_OS), U11.PAD (GND), U12.21 (OBUF_OS), U12.PAD (GND); also elsewhere on the board
/Level triggering/LTRIG_SAMPOUT_N: C147.2; also elsewhere on the board
/Level triggering/LTRIG_SAMPOUT_P: C146.2; also elsewhere on the board
/Phase control/CLKIN0_N: U11.4 (Q2_P); also elsewhere on the board
/Phase control/CLKIN0_P: U11.5 (Q2_N); also elsewhere on the board
/Phase control/CLKIN1_N: U11.10 (Q4_P); also elsewhere on the board
/Phase control/CLKIN1_P: U11.11 (Q4_N); also elsewhere on the board
/SAMP_MUXSEL0: R129.1, U12.18 (MUX_SEL); also elsewhere on the board
/SAMP_MUXSEL1: R128.1, U11.18 (MUX_SEL); also elsewhere on the board
/Sample clock muxing/BUF2_IN_SEL: JP2.2, U11.13 (IBUF_TS)
/Sample clock muxing/BUF3_IN_SEL: JP3.2, U12.13 (IBUF_TS)
/Sample clock muxing/CLKOUT2_N: J15.1 (In), U11.7 (Q3_P)
/Sample clock muxing/CLKOUT2_P: J16.1 (In), U11.8 (Q3_N)
/Sample clock muxing/EXT_CLK_AC_N: C205.1, U12.17 (CLKIN0_P)
/Sample clock muxing/EXT_CLK_AC_P: C206.1, U12.14 (CLKIN0_N)
/Sample clock muxing/EXT_SAMPCLK_N: C155.2; also elsewhere on the board
/Sample clock muxing/EXT_SAMPCLK_P: C156.2; also elsewhere on the board
/Sample clock muxing/LVL_CLK_AC_N: C147.1, U11.20 (CLKIN1_P)
/Sample clock muxing/LVL_CLK_AC_P: C146.1, U11.19 (CLKIN1_N)
/Sample clock muxing/MUXCLK0_AC_N: C149.1, U11.17 (CLKIN0_P)
/Sample clock muxing/MUXCLK0_AC_P: C148.1, U11.14 (CLKIN0_N)
/Sample clock muxing/MUXCLK0_N: C149.2, U12.23 (Q0_P)
/Sample clock muxing/MUXCLK0_P: C148.2, U12.24 (Q0_N)
/Sample clock muxing/MUXCLK1_AC_N: C155.1, U12.20 (CLKIN1_P)
/Sample clock muxing/MUXCLK1_AC_P: C156.1, U12.19 (CLKIN1_N)
/Sample clock muxing/PLL_SAMPCLK_N: C205.2; also elsewhere on the board
/Sample clock muxing/PLL_SAMPCLK_P: C206.2; also elsewhere on the board
unnamed: C154.1, U11.15 (VREF_AC), U11.16 (VTH)
unnamed: C157.1, U12.15 (VREF_AC), U12.16 (VTH)

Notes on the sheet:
Muxed clock/trigger signal for debugging or external DAQ hardware
Swap P/N for easier layout on input and output
